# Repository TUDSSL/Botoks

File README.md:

# Botoks

Botoks is a batteryless timekeeping sensor that operates intermittently
harvesting ambient energy.  Botoks's hardware and software components enable IoT
applications that require precise and intermittency-safe timekeeping.  Both
hardware design and software stack are open-source.

The *cascaded hierarchical remanence timekeeper* (CHRT) embedded on Botoks is a
novel remanence timekeeper architecture.  In principle, capacitive remanence
timekeepers are simple RC circuits whose energy level is converted into time.
To know more about them and the CHRT, refer to our paper (to be made public) and
[the docs][docs].

The sensor is based on an MSP430 ultra-low-power, FRAM-enabled microcontroller
(MSP430FR5994), and currently the software stack only supports this MCU.

<!--=========================================================================-->

## Project Layout

```
apps/               ## Applications' source code
bin/                ## Compiled applications
config/             ## Various configuration files
docs/               ## Source documentation
external/           ## MSP430 base drivers
libs/               ## Core Botoks's libraries
platforms/          ## GPIO pin mappings
scripts/            ## Botoks's calibration scripts
```

<!--=========================================================================-->

## Usage

Botoks's code can be built installing the MSP430-GCC toolchain, or using a
preconfigured Docker container.  Opting for the Docker container has the
advantage of not having to install the toolchain, but requires you to mount the
directory of the project into the container.

Executables can be uploaded and debugged using UniFlash or Code Composer Studio
(CCS).  The former method is easier to script, whilst the latter gives you
access to a graphical IDE.

The following versions of CMake, MSP430-GCC and UniFlash were tested, but other
versions might work as well.

<!-- For artifact: -->
<!-- CMake 3.15.5 -->
<!-- MSP430-GCC 6.1.1.0 -->
<!-- MSP430-GCC Support Files 1.208 -->
<!-- MSPDebug 0.25 -->

| Software   | Version |                      |
|:-----------|:--------|:---------------------|
| CMake      | 3.13    | [download][cmake]    |
| MSP430-GCC | 8.3.0   | [download][mspgcc]   |
| UniFlash   | 5.2.0   | [download][uniflash] |

### Building with the Docker container

You can use the `build_with_docker.sh` script to build all applications inside a
Docker container.  Install `docker` on your machine and start/enable the
`docker` daemon.  Moreover, make sure that you can `docker` commands **without**
root privileges (check [here][docker-no-root]).  The script uses [this Docker
image][docker-image] to build applications inside a Docker container
pre-configured with CMake and the MSP430-GCC toolchain.

You can pass `-t <target>` to the script to specify a target for `make`.  For
instance, to build all projects and install the generated executables in the
`bin/` folder of this repository, run

```bash
$ ./build_with_docker.sh -t install
```

### Building without the Docker container

First of all, install CMake and the MSP430-GCC toolchain.  CMake can be
installed using your OS's package manager, though the latest version might not
be available.  In that case, download the binaries using the link above.  As for
the GCC toolchain, you can use the provided `install_toolchain.sh` script to
download and install toolchain and support files.

To install, do

```bash
$ MSP430_GCC_OS=linux64   # can be 'linux32' or 'macos' instead
$ INSTALL_PREFIX=~/ti     # where to install the toolchain
$ ./install_toolchain.sh
```

This will download toolchain and other support files from TI's website, and
install them at `$INSTALL_PREFIX/msp430-gcc`.  Then, assign the environment
variable `MSP430_TOOLCHAIN_PATH` the absolute path to the root directory of the
toolchain, e.g.

```bash
$ export MSP430_TOOLCHAIN_PATH=~/ti/msp430-gcc
```

Finally, to build all projects, do

```bash
$ git clone https://github.com/TUDSSL/Botoks.git
$ cd Botoks
$ mkdir build && cd build
$ cmake ..
$ make
```

Then run `make install` to build all projects and install the generated
executables in the `bin/` folder of this repository.  To build applications
individually, run `make <app-name>`.

### Running applications

First, connect Botoks to a debugger capable of debugging the MSP430 line of
products.  Then power Botox using the auxiliary power connector on the PCB.  The
voltage provided needs to be between 3.4 and 5V.

To upload an application install [UniFlash][uniflash].  As of now, all scripts
assume UniFlash is installed at `/opt/ti/uniflash`.  From the project's
directory root, run:

```bash
$ ./flash.sh bin/<app-name>.out
```

The serial output can now be monitored using your favorite serial monitor (e.g.,
`picocom`) with a baudrate of 19200.

```bash
$ picocom /dev/ttyACM1 -b 19200 --imap lfcrlf
```

### Calibration

For the calibration procedure please refer to [the docs][docs].  Running the
calibration procedure requires a licensed version of [MATLAB][matlab] and the
serial terminal `picocom`.

<!--=========================================================================-->

## Documentation

The Docker container comes with all the dependencies to build the documentation.
Simply run

```bash
$ ./build_with_docker.sh -t docs
```

and find the HTML documentation in `build/docs/html`.

<!--=========================================================================-->

## Hardware

The hardware is designed in [KiCad][kicad], however, PDF schematics and gerbers
are available in the [hardware][hardware] folder.

<!--=========================================================================-->

[paper]: dl.link
[docs]: #documentation
[cmake]: https://cmake.org/download/
[mspgcc]: http://software-dl.ti.com/msp430/msp430_public_sw/mcu/msp430/MSPGCC/latest/index_FDS.html
[uniflash]: http://www.ti.com/tool/UNIFLASH
[docker-no-root]: https://docs.docker.com/install/linux/linux-postinstall/#manage-docker-as-a-non-root-user
[docker-image]: https://hub.docker.com/r/cdelledonne/msp430-gcc
[matlab]: https://www.mathworks.com/products/matlab.html
[kicad]: http://www.kicad.org/
[hardware]: ./hardware

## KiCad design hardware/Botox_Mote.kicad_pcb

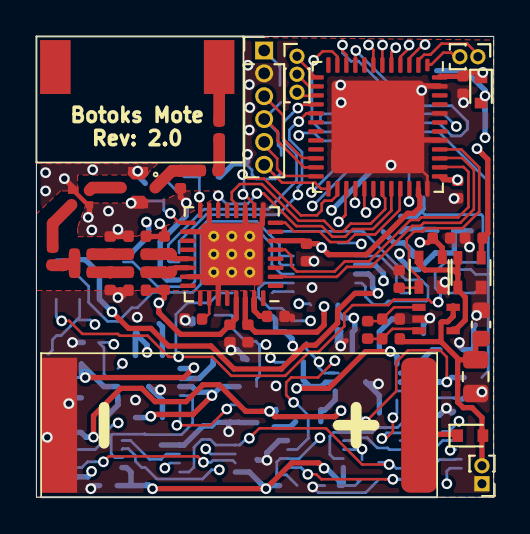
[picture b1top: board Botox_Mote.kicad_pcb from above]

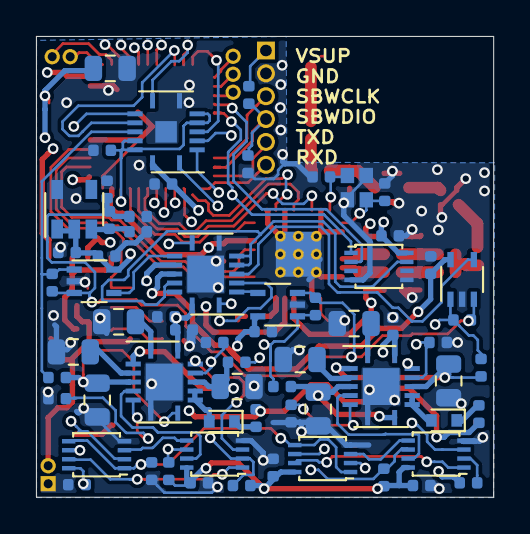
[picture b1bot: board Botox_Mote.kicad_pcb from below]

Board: 4 copper layers, 25.4 x 25.6 mm, 109 parts (65 on the bottom side), 91 nets.

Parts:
AE1: W3016
C1, C4, C5, C6, C7, C22, C23, C24, C27, C28, C29, C30, C31, C32, C33, C34, C37, C38, C44, C45: 100nF; C_0402_1005Metric
C2, C3, C17, C21, C39, C43: DNP; C_0402_1005Metric
C8, C11: 39pF; C_0402_1005Metric
C9, C10, C14: 100pF; C_0402_1005Metric
C12, C13: 0.7pF; C_0402_1005Metric
C15, C18: 2.2uF; C_0402_1005Metric
C16: C; C_0402_1005Metric
C20: 10u; C_0805_2012Metric
C25, C35: 2.2 / 220nF; C_0805_2012Metric
C26, C36: 22 nF / 2.2uF; C_0805_2012Metric
C40: 2.2nF; C_0402_1005Metric
C41: 22uF; C_0603_1608Metric
C42: 100uF; C_0805_2012Metric
D1, D2, D3, D4: BAS40-02V-V-G-08; D_SOD-523
F1: SF16-0868M4
J1: 952-3602-ND; PinHeader_1x06_P1.27mm_Vertical
J2: Conn_01x03; PinHeader_1x03_P1.00mm_Vertical
J3, J5: Conn_01x02; PinHeader_1x02_P1.00mm_Vertical
J4: MM8030-2610; MM8030
L1, L2: 8.7nH; L_0402_1005Metric
L3, L4: 39nH; L_0402_1005Metric
L5: 19nH; L_0402_1005Metric
L6: 7.5nH; L_0402_1005Metric
R1: 49.9k ±1%; R_0402_1005Metric
R2, R4, R5, R6, R7, R8, R11, R22, R23, R24, R25: 10M; R_0402_1005Metric
R9, R10, R26, R27, R37: 100; R_0402_1005Metric
R13, R14, R30, R31: 22M; R_0805_2012Metric
R15: 9.1M; R_0402_1005Metric
R16: 2.4M; R_0402_1005Metric
R32: 47k; R_0402_1005Metric
R33: 1.5M; R_0402_1005Metric
R34: 360k; R_0402_1005Metric
R35: 1.1M; R_0402_1005Metric
R36: 10k; R_0402_1005Metric
SC1: KXOB25-02X8F
U1, U18: S-1313A22-N4T1U3; SC-82AB
U2: ZL70550; QFN-32-1EP_5x5mm_P0.5mm_EP3.45x3.45mm_ThermalVias_0.3mm_Dri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
U3, U6, U10, U14: TS3A4751; Texas_S-PVQFN-N14
U4, U11, U12: SN74AUP2G79DCU; VSSOP-8_2.4x2.1mm_P0.5mm
U5, U13: SN74AUP2G00DCU; VSSOP-8_2.4x2.1mm_P0.5mm
U7: MCP1810T-12; SOT-23-5
U8, U9, U17: TLV3691IDCK; Texas_R-PDSO-G5
U15: MSP430FR5994IRGZ; QFN-48-1EP_7x7mm_P0.5mm_EP5.15x5.15mm
U16: MIC841HYC5; SC70-5
Y1: ECS-240-8-37CKM; ECX-1637

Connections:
/CHRT/ADC0: U3.2, U15.3
/CHRT/ADC1: U3.4, U15.11
/CHRT/ADC2: U3.10, U15.9
/CHRT/ADC3: U3.8, U15.10
/CHRT/CAS_EN: U11.2, U15.16
/CHRT/Cascade/EN_CASCADE: U10.5, U10.6, U10.12, U10.13, U11.7
/CHRT/Cascade/VINT: C15.1, C27.2, C28.2, C29.2, U7.1, U7.2, U8.5, U9.5, U10.11, U17.5
/CHRT/Cascade/VREF: C17.1, C21.2, C39.2, C43.2, R15.2, R16.1, U8.3, U9.3, U17.3
/CHRT/EN_CHR_0: R23.1, U14.6, U15.5
/CHRT/EN_CHR_1: R24.1, U14.12, U15.7
/CHRT/EN_CHR_2: R6.1, U6.6, U15.28
/CHRT/EN_CHR_3: R7.1, U6.12, U15.27
/CHRT/EN_TIME_0: U12.2, U15.6
/CHRT/EN_TIME_1: U12.6, U15.4
/CHRT/EN_TIME_2: U4.2, U15.30
/CHRT/EN_TIME_3: U4.6, U15.29
/CHRT/HRT1/EN_CAS_TIME_0: R22.2, U13.2
/CHRT/HRT1/EN_CAS_TIME_1: R25.2, U10.1, U13.6
/CHRT/HRT1/VCHARGE: D3.1, R36.1
/CHRT/HRT2/EN_CAS_TIME_0: R5.2, U5.2, U10.3
/CHRT/HRT2/EN_CAS_TIME_1: R8.2, U5.6, U10.8
/CHRT/HRT2/VCHARGE: D2.1, R37.1
/CHRT/INT_ADC0: C21.1, R26.2, U3.1, U8.1
/CHRT/INT_ADC1: C39.1, R27.2, U3.3, U9.1
/CHRT/INT_ADC2: C43.1, R9.2, U3.11, U17.1
/CHRT/INT_ADC3: R10.2, U3.9
/CHRT/VCHARGE: C44.1, R36.2, R37.2, U18.3
/CHRT/VIN: C20.1, C22.2, C23.2, C24.2, C30.1, C31.1, C32.2, C33.2, C34.2, C45.1, D1.2, R5.1, R8.1, R22.1, R25.1, U3.14, U4.8, U5.8, U6.14, U10.10, U10.14, U11.8, U12.8, U13.8, U14.14
/Harvester/VSOLAR: C41.1, C42.1, D4.2, J5.2, R33.1, U16.5
/MCU/BCL_UART_RXD: J1.6, U15.25
/MCU/BCL_UART_TXD: J1.5, U15.24
/MCU/CAS_CHARGE: R11.1, U15.40, U18.1
/MCU/CAS_CLK: R4.1, U4.1, U4.5, U11.1, U12.1, U12.5, U15.17
/MCU/CAS_EN_ADC: R2.2, U3.5, U3.6, U3.12, U3.13, U15.34
/MCU/SBWTCK: J1.3, U15.22
/MCU/SBWTDIO: C40.1, J1.4, R32.2, U15.23
/MCU/ZL_RST: U2.2, U15.39
/VHARVESTER: U1.1, U1.4, U16.4, U18.4
/VSUP: C1.1, C37.1, C38.1, D1.1, J1.1, R32.1, U1.3, U15.37, U15.48
/ZL70550/CLK: U2.10, U15.26
/ZL70550/IRQ: U2.5, U15.38
/ZL70550/MISO: U2.14, U15.32
/ZL70550/MOSI: U2.12, U15.31
/ZL70550/SEL: U2.8, U15.33
/ZL70550/VSUP: C4.2, C5.2, U2.6, U2.30, U15.35
GND: C1.2, C2.1, C3.1, C4.1, C5.1, C6.2, C7.2, C8.1, C11.1, C12.1, C15.2, C16.1, C17.2, C18.2, C20.2, C22.1, C23.1, C24.1, C25.2, C26.2, C27.1, C28.1, C29.1, C30.2, C31.2, C32.1, C33.1, C34.1, C35.2, C36.2, C37.2, C38.2, C40.2, C41.2, C42.2, C44.2, C45.2, F1.2, F1.4, J1.2, J4.0, J5.1, L3.2, R1.2, R2.1, R4.2, R6.2, R7.2, R11.2, R13.2, R14.2, R16.2, R23.2, R24.2, R30.2, R31.2, R35.2, SC1.2, U1.2, U2.9, U2.11, U2.15, U2.18, U2.23, U2.27, U2.33, U3.7, U3.15, U4.4, U5.4, U6.7, U6.15, U7.5, U8.2, U9.2, U10.7, U10.15, U11.4, U11.5, U11.6, U12.4, U13.4, U14.7, U14.15, U15.36, U15.41, U15.44, U15.47, U15.49, U16.2, U17.2, U18.2, Y1.2, Y1.4
unnamed: AE1.1, L6.2
unnamed: C2.2, U2.17, Y1.1
unnamed: C3.2, U2.16, Y1.3
unnamed: C6.1, U2.31
unnamed: C9.2, L1.2, U2.22
unnamed: C10.1, C13.2, L3.1
unnamed: C10.2, L2.1, U2.21
unnamed: C9.1, C12.2, L4.1
unnamed: C13.1, C14.2, L4.2
unnamed: C14.1, F1.1
unnamed: C16.2, J4.1, L5.1
unnamed: C18.1, R15.1, U7.3
unnamed: C25.1, R9.1, U6.4, U6.8
unnamed: C26.1, R10.1, U6.2, U6.11
unnamed: C35.1, R26.1, U14.4, U14.8
unnamed: C36.1, R27.1, U14.2, U14.11
unnamed: D2.2, U6.9, U6.10
unnamed: D3.2, U14.9, U14.10
unnamed: D4.1, SC1.1
unnamed: F1.3, J4.2
unnamed: J2.1, U15.13
unnamed: J2.2, U15.14
unnamed: J2.3, U15.15
unnamed: J3.1, U15.2
unnamed: J3.2, U15.1
unnamed: L5.2, L6.1
unnamed: R1.1, U2.26
unnamed: R13.1, U6.3
unnamed: R14.1, U6.1
unnamed: R30.1, U14.3
unnamed: R31.1, U14.1
unnamed: R33.2, R34.1, U16.3
unnamed: R34.2, R35.1, U16.1
unnamed: U4.3, U5.5
unnamed: U4.7, U5.1
unnamed: U5.3, U6.13
unnamed: U5.7, U6.5
unnamed: U8.4, U10.2
unnamed: U9.4, U10.4
unnamed: U10.9, U17.4
unnamed: U12.3, U13.5
unnamed: U12.7, U13.1
unnamed: U13.3, U14.13
unnamed: U13.7, U14.5
VDDA: C7.1, C8.2, C11.2, L1.1, L2.2, U2.29

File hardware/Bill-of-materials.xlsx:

Qty | Reference(s) | Value | Footprint | Datasheet | MPN | Digikey | Mouser
1 | AE1 | W3016 | jaspers_footprints:W3016 | https://productfinder.pulseeng.com/product/W3016 | W3016
20 | C1, C4, C5, C6, C7, C22, C23, C24, C27, C28, C29, C30, C31, C32, C33, C34, C37,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 | 100nF | Capacitor_SMD:C_0402_1005Metric | ~ | GCM155R71C104KA55D | 490-4759-1-ND | 81-GCM155R71C104KA5D
6 | C2, C3, C17, C21, C39, C43 | DNP | Capacitor_SMD:C_0402_1005Metric | ~
2 | C8, C11 | 39pF | Capacitor_SMD:C_0402_1005Metric | ~ | 04025A390JAT2A | 478-1077-1-ND | 581-04025A390J
3 | C9, C10, C14 | 100pF | Capacitor_SMD:C_0402_1005Metric | ~ | GCM1555C1H101JA16D | 490-10669-1-ND | 81-GCM1555C1H101JA6D
2 | C12, C13 | 0.7pF | Capacitor_SMD:C_0402_1005Metric | ~ | 500R07S0R7AV4T | 712-1249-1-ND | 609-500R07S0R7AV4T
2 | C15, C18 | 2.2uF | Capacitor_SMD:C_0402_1005Metric | ~ | GRM155R61C225KE11D | 490-10695-1-ND | 81-GRM155R61C225KE1D
1 | C16 | C | Capacitor_SMD:C_0402_1005Metric | ~ | LQW15AN4N3G8ZD | 490-15466-1-ND
1 | C20 | 10u | Capacitor_SMD:C_0805_2012Metric | ~ | CL21A106KPFNNNG | 1276-6456-1-ND
1 | C35 | 2.2nF | Capacitor_SMD:C_0805_2012Metric | ~ | GRM2165C1H222FA01D | 490-6443-1-ND | 81-GRM2165C1H222FA1D
1 | C36 | 22nF | Capacitor_SMD:C_0805_2012Metric | ~ | GRM21B5C1H223JA01L | 490-1644-1-ND | 81-GRM215C1H223JA01L
1 | C25 | 220nF | Capacitor_SMD:C_0805_2012Metric | ~ | GCM21BR71H224KA37L | 490-4970-1-ND | 81-GCM21BR71H224K37L
1 | C26 | 2.2uF | Capacitor_SMD:C_0805_2012Metric | ~ | GCM21BR71E225KA73L | 490-4787-1-ND | 81-GCM21BR71E225KA3L
1 | C40 | 2.2nF | Capacitor_SMD:C_0402_1005Metric | ~ | GCM155R71H222KA37D | 490-4914-1-ND | 81-GCM155R71H222K37D
1 | C41 | 22uF | Capacitor_SMD:C_0603_1608Metric | ~ | GRM187R61A226ME15D | 490-13243-1-ND | 81-GRM187R61A226ME5D
1 | C42 | 100uF | Capacitor_SMD:C_0805_2012Metric | ~ | GRM21BR60J107ME15L | 490-13981-1-ND | 81-GRM21BR60J107ME5L
4 | D1, D2, D3, D4 | BAS40-02V-V-G-08 | Diode_SMD:D_SOD-523 | http://www.vishay.com/docs/82391/bas4002v.pdf | BAS40-02V-V-G-08 | BAS40-02V-V-G-08GICT-ND | 78-BAS40-02V-V-G-08
1 | F1 | SF16-0868M4 | jaspers_footprints:SF16-0868M4 | https://global.kyocera.com/prdct/electro/product/pdf/sf14_sf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 | SF16-0868M4 | 478-6488-1-ND | 581-SF16-0868M4UU01
1 | J1 | 952-3602-ND | Connector_PinHeader_1.27mm:PinHeader_1x06_P1.27mm_Vertical | ~ | M50-3530642 | 952-3602-ND | 855-M50-3530642
1 | J2 | Conn_01x03 | Connector_PinHeader_1.00mm:PinHeader_1x03_P1.00mm_Vertical | ~ | SMH100-LPSE-S40-ST-BK | S9219-ND
2 | J3, J5 | Conn_01x02 | Connector_PinHeader_1.00mm:PinHeader_1x02_P1.00mm_Vertical | ~
1 | J4 | MM8030-2610 | jaspers_footprints:MM8030 |  | MM8030-2610 | 490-5907-1-ND‎ | 81-MM8030-2610RK0
2 | L1, L2 | 8.7nH | Inductor_SMD:L_0402_1005Metric | ~ | LQW15AN8N7G00D | 490-6851-1-ND | 81-LQW15AN8N7G00D
2 | L3, L4 | 39nH | Inductor_SMD:L_0402_1005Metric | ~ | LQW15AN39NG8ZD | 490-15413-1-ND | 81-LQW15AN39NG8ZD
1 | L5 | 19nH | Inductor_SMD:L_0402_1005Metric | ~ | LQW15AN19NG00D | 490-6778-1-ND | 81-LQW15AN19NG00D
1 | L6 | 7.5nH | Inductor_SMD:L_0402_1005Metric | ~ | LQW15AN7N5G00D | 490-6846-1-ND | 81-LQW15AN7N5G00D
1 | R1 | 49.9k ±1% | Resistor_SMD:R_0402_1005Metric | ~ | ERJ-2RKF4992X | P49.9KLCT-ND | 667-ERJ-2RKF4992X
11 | R2, R4, R5, R6, R7, R8, R11, R22, R23, R24, R25 | 10M | Resistor_SMD:R_0402_1005Metric | ~ | RC1005F106CS | 1276-3434-1-ND
5 | R9, R10, R26, R27, R37 | 100 | Resistor_SMD:R_0402_1005Metric | ~ | ERJ-2GEJ101X | P100JCT-ND | 667-ERJ-2GEJ101X
4 | R13, R14, R30, R31 | 22M | Resistor_SMD:R_0805_2012Metric | ~ | RMCF0805FT22M0 | RMCF0805FT22M0CT-ND
1 | R15 | 9.1M | Resistor_SMD:R_0402_1005Metric | ~ | ERJ-2GEJ915X | P9.1MJCT-ND | 667-ERJ-2GEJ915X
1 | R16 | 2.4M | Resistor_SMD:R_0402_1005Metric | ~ | ERJ-2GEJ245X | P2.4MJCT-ND | 667-ERJ-2GEJ245X
1 | R32 | 47k | Resistor_SMD:R_0402_1005Metric | ~ | ERJ-2GEJ473X | P47KJCT-ND | 667-ERJ-2GEJ473X
1 | R33 | 1.5M | Resistor_SMD:R_0402_1005Metric | ~ | ERJ-2GEJ155X | P1.5MJCT-ND | 667-ERJ-2GEJ155X
1 | R34 | 360k | Resistor_SMD:R_0402_1005Metric | ~ | ERJ-2RKF3603X | P360KLCT-ND | 667-ERJ-2RKF3603X
1 | R35 | 1.1M | Resistor_SMD:R_0402_1005Metric | ~ | AC0402FR-071M1L | YAG5647CT-ND | 603-AC0402FR-071M1L
1 | R36 | 10k | Resistor_SMD:R_0402_1005Metric | ~ | ERJ-2RKF1002X | P10.0KLCT-ND | 667-ERJ-2RKF1002X
1 | SC1 | KXOB25-02X8F | jaspers_footprints:KXOB25-02X8F | ~ | KXOB25-02X8F | KXOB25-02X8F-ND
2 | U1, U18 | S-1313A22-N4T1U3 | Package_TO_SOT_SMD:SC-82AB | https://www.ablic.com/en/doc/datasheet/voltage_regulator/S13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 | S-1313A22-N4T1U3 | 1662-2988-1-ND | 628-S-1313A22-N4T1U3
1 | U2 | ZL70550 | jaspers_footprints:QFN-32-1EP_5x5mm_P0.5mm_EP3.45x3.45mm_ThermalVias_0.3mm_Drill | https://www.microsemi.com/document-portal/doc_download/13581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 | ZL70550LDF1 |  | 494-ZL70550LDF1
4 | U3, U6, U10, U14 | TS3A4751 | Package_DFN_QFN:Texas_S-PVQFN-N14_ThermalVias | http://www.ti.com/general/docs/lit/getliterature.tsp?generic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 | TS3A4751RGYR | 296-24477-1-ND | 595-TS3A4751RGYR
3 | U4, U11, U12 | SN74AUP2G79DCU | Package_SO:VSSOP-8_2.4x2.1mm_P0.5mm | http://www.ti.com/lit/ds/symlink/sn74aup2g79.pdf | SN74AUP2G79DCUR | 296-25598-1-ND | 595-SN74AUP2G79DCUR
2 | U5, U13 | SN74AUP2G00DCU | Package_SO:VSSOP-8_2.4x2.1mm_P0.5mm | http://www.ti.com/lit/ds/symlink/sn74aup2g00.pdf | SN74AUP2G00DCUR | 296-36884-1-ND | 595-SN74AUP2G00DCUR
1 | U7 | MCP1810T-12 | Package_TO_SOT_SMD:SOT-23-5 | http://ww1.microchip.com/downloads/en/DeviceDoc/20005623B.pdf | MCP1810T-12 | - | 579-MCP1810T12IOT
3 | U8, U9, U17 | TLV3691IDCK | jaspers_footprints:Texas_R-PDSO-G5 | http://www.ti.com/lit/ds/symlink/tlv3691.pdf | TLV3691IDCKR | 296-37910-1-ND | 595-TLV3691IDCKR
1 | U15 | MSP430FR5994IRGZ | Package_DFN_QFN:QFN-48-1EP_7x7mm_P0.5mm_EP5.15x5.15mm_ThermalVias | http://www.ti.com/lit/ds/symlink/msp430fr5994.pdf | MSP430FR5994IRGZ | 296-48940-1-ND | 595-P430FR5994IRGZR
1 | U16 | MIC841HYC5 | jaspers_footprints:SC70-5 | http://ww1.microchip.com/downloads/en/DeviceDoc/20005758A.pdf | MIC841HYC5-TR | 576-2923-1-ND | 998-MIC841HYC5TR
1 | Y1 | ECS-240-8-37CKM | jaspers_footprints:ECX-1637 | https://www.ecsxtal.com/store/pdf/ecx-1637.pdf | ECS-240-8-37CKM | XC1543CT-ND | 520-ECS-240-8-37CKM

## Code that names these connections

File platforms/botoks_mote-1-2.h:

#ifndef INCLUDE_BOTOKS_H
#define INCLUDE_BOTOKS_H

// For logic analyzer
#define PRF_PORT J
#define DELAY_PIN 1
#define RADIO_PIN 2
#define RX_PKT_PIN 3

#define DBG_PORT 1
#define DEBUG_B 0
#define DBG_PWR_PORT 1
#define DEBUG_POWER_PIN 1

// Timer pin definitions
// GPIO pins
#define ADC_PORT 1
#define ADC_PIN_0 2
#define ADC_PIN_1 3
#define ADC_PIN_2 4
#define ADC_PIN_3 5

#define ADC_CHANNEL_PREFIX ADC12INCH_
#define ADC_CHANNEL_0 CONCAT(ADC_CHANNEL_PREFIX, ADC_PIN_0)
#define ADC_CHANNEL_1 CONCAT(ADC_CHANNEL_PREFIX, ADC_PIN_1)
#define ADC_CHANNEL_2 CONCAT(ADC_CHANNEL_PREFIX, ADC_PIN_2)
#define ADC_CHANNEL_3 CONCAT(ADC_CHANNEL_PREFIX, ADC_PIN_3)

#define CHARGE_PORT 3
#define CHARGE_PIN_0 0
#define CHARGE_PIN_1 2
#define CHARGE_PIN_2 4
#define CHARGE_PIN_3 6

#define TIME_EN_PORT 3
#define TIME_EN_PIN_0 1
#define TIME_EN_PIN_1 3
#define TIME_EN_PIN_2 5
#define TIME_EN_PIN_3 7

#define CAS_PORT 4
#define CAS_CLK_PIN 1
#define CAS_EN_PIN 0

#define CAS_LDO_PORT 2
#define CAS_LDO_EN 4

#define CAS_EN_ADC_PORT 1
#define CAS_EN_ADC_EN 0

// Radio pin definitions
#define zl70550_POWER_PORT 4
#define zl70550_POWER_PIN 6
// CSn pin
#define zl70550_CSn_PORT 4
#define zl70550_CSn_PIN 4

#define zl70550_RESETn_PORT 2
#define zl70550_RESETn_PIN 3

#define zl70550_IRQ_PORT 2
#define zl70550_IRQ_PIN 7

#define SPI_MOSI_PORT 1
#define SPI_MOSI_PIN 6
#define SPI_MISO_PORT 1
#define SPI_MISO_PIN 7
#define SPI_CLK_PORT 2
#define SPI_CLK_PIN 2
#define SPI_CS_PORT 2
#define SPI_CS_PIN 4

#endif /* INCLUDE_BOTOKS_H */

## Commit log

2020-01-21 Added CI config
2020-01-21 Updates [ci skip]
2020-01-21 Fix github pages rendering
2020-01-21 Added .nojekyll to CI script
2020-01-21 Fix .nojekyll path
2021-11-08 Update README.md
    https://forum.kicad.info/t/warning-avoid-all-links-to-kicad-pcb-org-use-kicad-org/31521
